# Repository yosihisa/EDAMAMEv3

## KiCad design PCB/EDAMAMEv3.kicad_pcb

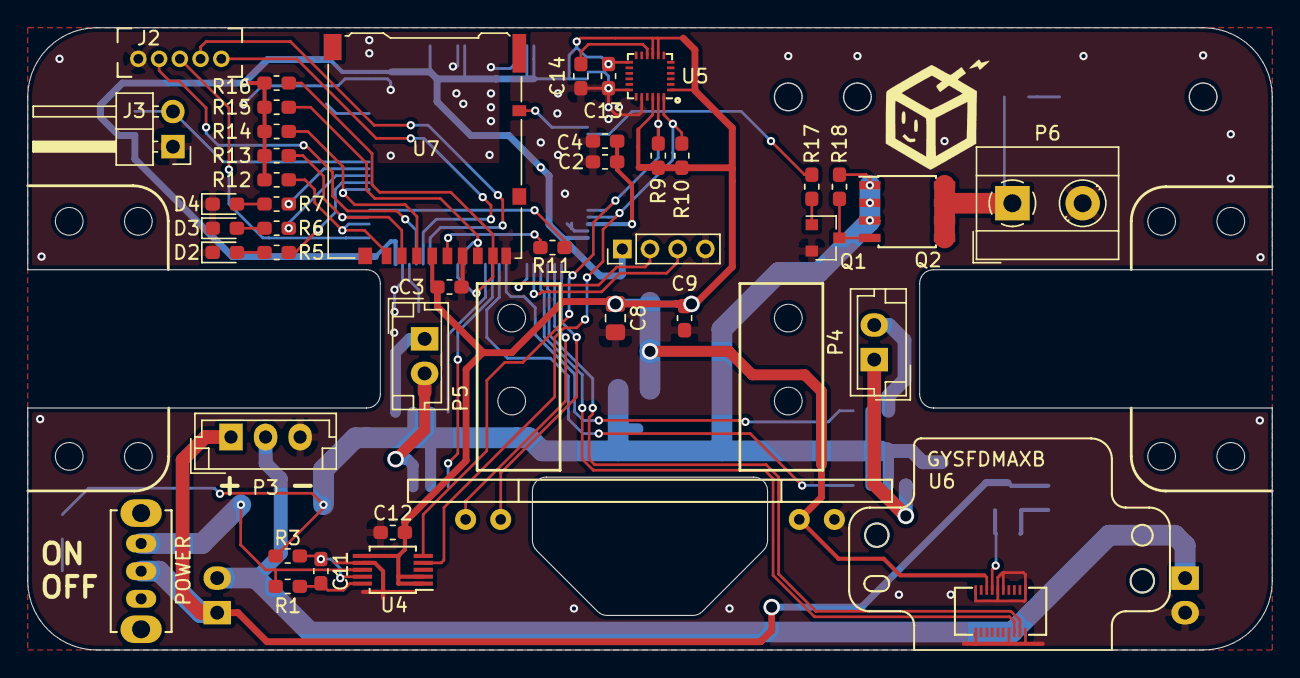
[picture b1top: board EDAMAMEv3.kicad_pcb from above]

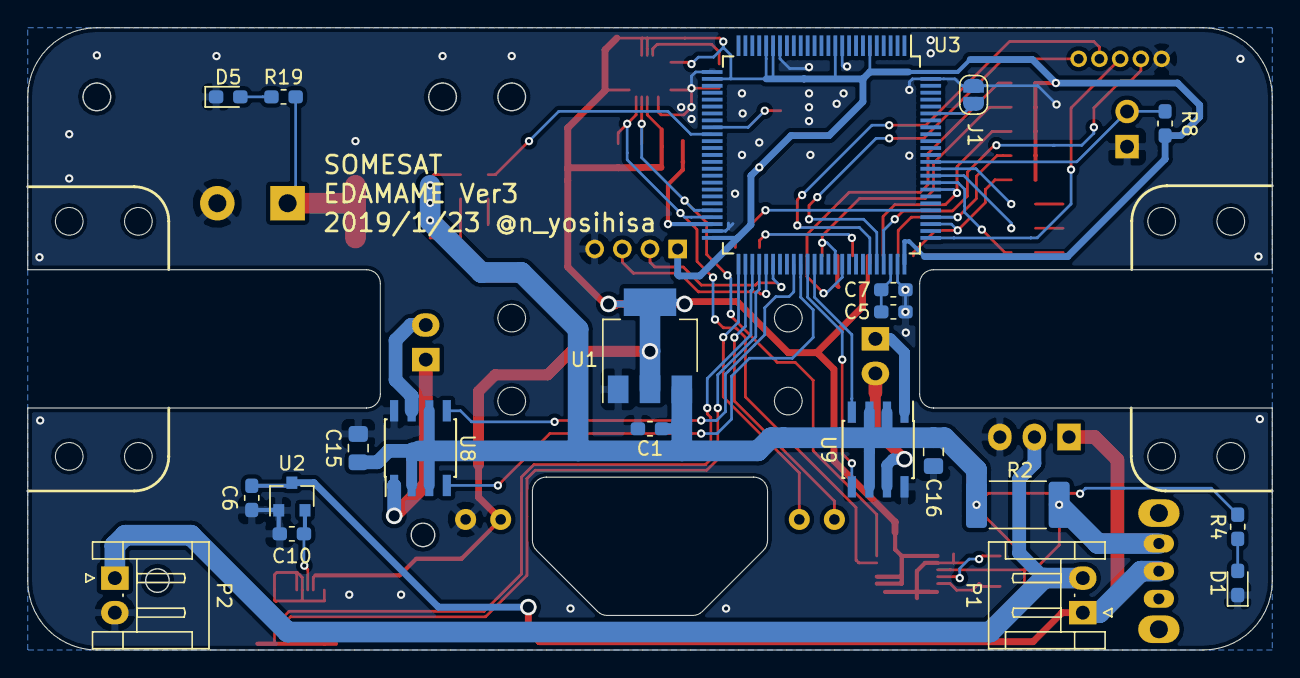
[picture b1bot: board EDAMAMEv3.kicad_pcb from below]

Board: 2 copper layers, 89.9 x 44.9 mm, 63 parts (21 on the bottom side), 54 nets.

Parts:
C1, C3, C4, C7, C9, C11, C12, C13, C14: 0.1u; C_0603_1608Metric_Pad1.05x0.95mm_HandSolder
C2, C5: 2.2u; C_0603_1608Metric_Pad1.05x0.95mm_HandSolder
C6, C10: 1u; C_0603_1608Metric_Pad1.05x0.95mm_HandSolder
C8, C15, C16: 10u; C_0805_2012Metric_Pad1.15x1.40mm_HandSolder
D1, D2, D3, D4, D5: LED; LED_0603_1608Metric_Pad1.05x0.95mm_HandSolder
J1: BOOT0; SolderJumper-2_P1.3mm_Open_RoundedPad1.0x1.5mm
J2: Debug; STlink
J3: FLIGHT_PIN; PinHeader_1x02_P2.54mm_Horizontal
J4: WiFi; ZUNDA_WIRELESS
J5: C1098; Pin_Header_Straight_1x04_Pitch2.00mm
P1: LiPo1; JST_EH_S02B-EH_1x02_P2.50mm_Horizontal
P2: LiPo2; JST_EH_S02B-EH_1x02_P2.50mm_Horizontal
P3: CHARGE; JST_EH_B03B-EH-A_1x03_P2.50mm_Vertical
P4: MOTOR_R; JST_EH_B02B-EH-A_1x02_P2.50mm_Vertical
P5: MOTOR_L; JST_EH_B02B-EH-A_1x02_P2.50mm_Vertical
P6: NICHROME; TerminalBlock_MetzConnect_Type101_RT01602HBWC_1x02_P5.08mm_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
Q1: 2SC2712; SOT-23
Q2: FDS4675; SOIC-8_3.9x4.9mm_P1.27mm
R1, R3: 10; R_0603_1608Metric_Pad1.05x0.95mm_HandSolder
R2: 10m; R_2512_6332Metric_Pad1.52x3.35mm_HandSolder
R4, R5, R6, R7, R19: 1k; R_0603_1608Metric_Pad1.05x0.95mm_HandSolder
R8, R18: 10k; R_0603_1608Metric_Pad1.05x0.95mm_HandSolder
R9, R10: 2.2k; R_0603_1608Metric_Pad1.05x0.95mm_HandSolder
R11: 47; R_0603_1608Metric_Pad1.05x0.95mm_HandSolder
R12, R13, R14, R15, R16: 22K; R_0603_1608Metric_Pad1.05x0.95mm_HandSolder
R17: 100; R_0603_1608Metric_Pad1.05x0.95mm_HandSolder
SW1: POWER; SS-12D01-VG4
U1: ADP3338AKCZ-3.3; SOT-223-3_TabPin2
U2: MCP1703AT-3302E/CB; SOT-23
U3: STM32F767VITx; LQFP-100_14x14mm_P0.5mm
U4: INA226; MSOP-10_3x3mm_P0.5mm
U5: MPU-9250; QFN-24_3x3mm_P0.4mm
U6: GYSFDMAXB
U7: microSD; microSD_HC_Hirose_DM3AT-SF-PEJM5
U8, U9: BD6231F; SOIC-8_3.9x4.9mm_P1.27mm

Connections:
+3V3: C3.1, C8.1, C9.1, C12.2, C13.1, J4.3, J5.1, R8.1, R9.2, R10.2, R12.2, R13.2, R14.2, R15.2, R16.2, U1.2, U3.6, U3.11, U3.20, U3.21, U3.27, U3.50, U3.75, U3.100, U4.1, U4.2, U4.6, U5.1, U5.8, U5.9, U5.13, U5.22, U6.16, U7.4
+BATT: C1.1, C15.1, C16.1, Q2.1, Q2.2, Q2.3, R2.1, R3.2, R4.2, R18.2, U1.3, U8.2, U8.3, U8.6, U9.2, U9.3, U9.6
/CAMERA_RX: J5.3, U3.55
/CAMERA_TX: J5.2, U3.56
/FLIGHT_PIN: J3.2, R8.2, U3.87
/GPS_BACKUP: C10.1, U2.2, U6.14
/GPS_RX: U3.53, U6.3
/GPS_TX: U3.54, U6.5
/I2C_SCL: R9.1, U3.46, U4.5, U5.23
/I2C_SDA: R10.1, U3.47, U4.4, U5.24
/LED1: R5.2, U3.84
/LED2: R6.2, U3.85
/LED3: R7.2, U3.86
/MOTOR_LF: U3.62, U9.4
/MOTOR_LR: U3.61, U9.5
/MOTOR_RF: U3.59, U8.5
/MOTOR_RR: U3.60, U8.4
/NICHROME: R17.2, U3.35
/PC_RX: J2.1, U3.71
/PC_TX: J2.2, U3.70
/SD: U3.34, U7.10
/SDIO_CK: R11.2, U3.80
/SDIO_CMD: R14.1, U3.83, U7.3
/SDIO_D0: R15.1, U3.65, U7.7
/SDIO_D1: R16.1, U3.66, U7.8
/SDIO_D2: R12.1, U3.78, U7.1
/SDIO_D3: R13.1, U3.79, U7.2
/SWCLK: J2.3, U3.76
/SWDIO: J2.4, U3.72
/WiFi_RX: J4.1, U3.52
/WiFi_TX: J4.2, U3.51
GND: C1.2, C2.2, C3.2, C4.2, C5.2, C6.2, C7.2, C8.2, C9.2, C10.2, C12.1, C13.2, C14.2, C15.2, C16.2, D1.1, D2.1, D3.1, D4.1, D5.1, J1.1, J2.5, J3.1, J4.4, J5.4, P2.2, P3.3, P6.2, Q1.2, U1.1, U2.1, U3.10, U3.19, U3.26, U3.49, U3.74, U3.99, U4.7, U5.18, U5.20, U6.1, U6.2, U6.7, U6.10, U6.12, U6.19, U6.20, U7.6, U7.9, U8.8, U9.8
unnamed: C2.1, C4.1, U3.48
unnamed: C5.1, C7.1, U3.73
unnamed: C6.1, P1.1, P3.1, SW1.2, U2.3
unnamed: C11.1, R3.1, U4.9
unnamed: C11.2, R1.1, U4.10
unnamed: C14.1, U5.10
unnamed: D1.2, R4.1
unnamed: D2.2, R5.1
unnamed: D3.2, R6.1
unnamed: D4.2, R7.1
unnamed: D5.2, R19.1
unnamed: J1.2, U3.94
unnamed: P1.2, P2.1, P3.2
unnamed: P4.1, U8.1
unnamed: P4.2, U8.7
unnamed: P5.1, U9.1
unnamed: P5.2, U9.7
unnamed: P6.1, Q2.5, Q2.6, Q2.7, Q2.8, R19.2
unnamed: Q1.1, R17.1
unnamed: Q1.3, Q2.4, R18.1
unnamed: R1.2, R2.2, SW1.3, U4.8
unnamed: R11.1, U7.5

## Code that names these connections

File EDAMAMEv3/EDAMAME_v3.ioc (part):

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Mcu.Name=STM32F767VITx
Mcu.Package=LQFP100
Mcu.UserName=STM32F767VITx
PA11.Mode=Asynchronous
PA11.Signal=UART4_RX
PA12.Mode=Asynchronous
PA12.Signal=UART4_TX
PA13.Mode=Serial_Wire
PA13.Signal=SYS_JTMS-SWDIO
PA14.Mode=Serial_Wire
PA14.Signal=SYS_JTCK-SWCLK
PB0.GPIOParameters=GPIO_Label
PB0.GPIO_Label=SD
PB0.Signal=GPIO_Input
PB1.Signal=S_TIM3_CH4
PB10.Mode=I2C
PB10.Signal=I2C2_SCL
PB11.Mode=I2C
PB11.Signal=I2C2_SDA
PB12.Mode=Asynchronous
PB12.Signal=UART5_RX
PB13.Mode=Asynchronous
PB13.Signal=UART5_TX
PB14.Mode=Asynchronous
PB14.Signal=USART1_TX
PB15.Mode=Asynchronous
PB15.Signal=USART1_RX
PC10.Mode=SD_4_bits_Wide_bus
PC10.Signal=SDMMC1_D2
PC11.Mode=SD_4_bits_Wide_bus
PC11.Signal=SDMMC1_D3
PC12.Mode=SD_4_bits_Wide_bus
PC12.Signal=SDMMC1_CK
PC8.Mode=SD_4_bits_Wide_bus
PC8.Signal=SDMMC1_D0
PC9.Mode=SD_4_bits_Wide_bus
PC9.Signal=SDMMC1_D1
PD12.Signal=S_TIM4_CH1
PD13.Signal=S_TIM4_CH2
PD14.Signal=S_TIM4_CH3
PD15.Signal=S_TIM4_CH4
PD2.Mode=SD_4_bits_Wide_bus
PD2.Signal=SDMMC1_CMD
PD3.GPIOParameters=GPIO_Label
PD3.GPIO_Label=LED3
PD3.Signal=GPIO_Output
PD4.GPIOParameters=GPIO_Label
PD4.GPIO_Label=LED2
PD4.Signal=GPIO_Output
PD5.GPIOParameters=GPIO_Label
PD5.GPIO_Label=LED1
PD5.Signal=GPIO_Output
PD6.GPIOParameters=GPIO_Label
PD6.GPIO_Label=flightPin
PD6.Signal=GPIO_Input
PD8.Mode=Asynchronous
PD8.Signal=USART3_TX
PD9.Mode=Asynchronous
PD9.Signal=USART3_RX
RCC.HSE_VALUE=25000000
RCC.SYSCLKFreq_VALUE=216000000
RCC.SYSCLKSource=RCC_SYSCLKSOURCE_PLLCLK
board=custom

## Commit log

2019-01-20 move form SOMESAT_2019
2019-01-20 move
2019-02-07 Reanme src
2019-02-07 Add PCB
2019-02-07 Add BBM
2019-02-08 Add Jpeg decod benchmark
2019-02-10 Update C1098
2019-02-21 del .vs
2019-03-04 Add edamame.c
